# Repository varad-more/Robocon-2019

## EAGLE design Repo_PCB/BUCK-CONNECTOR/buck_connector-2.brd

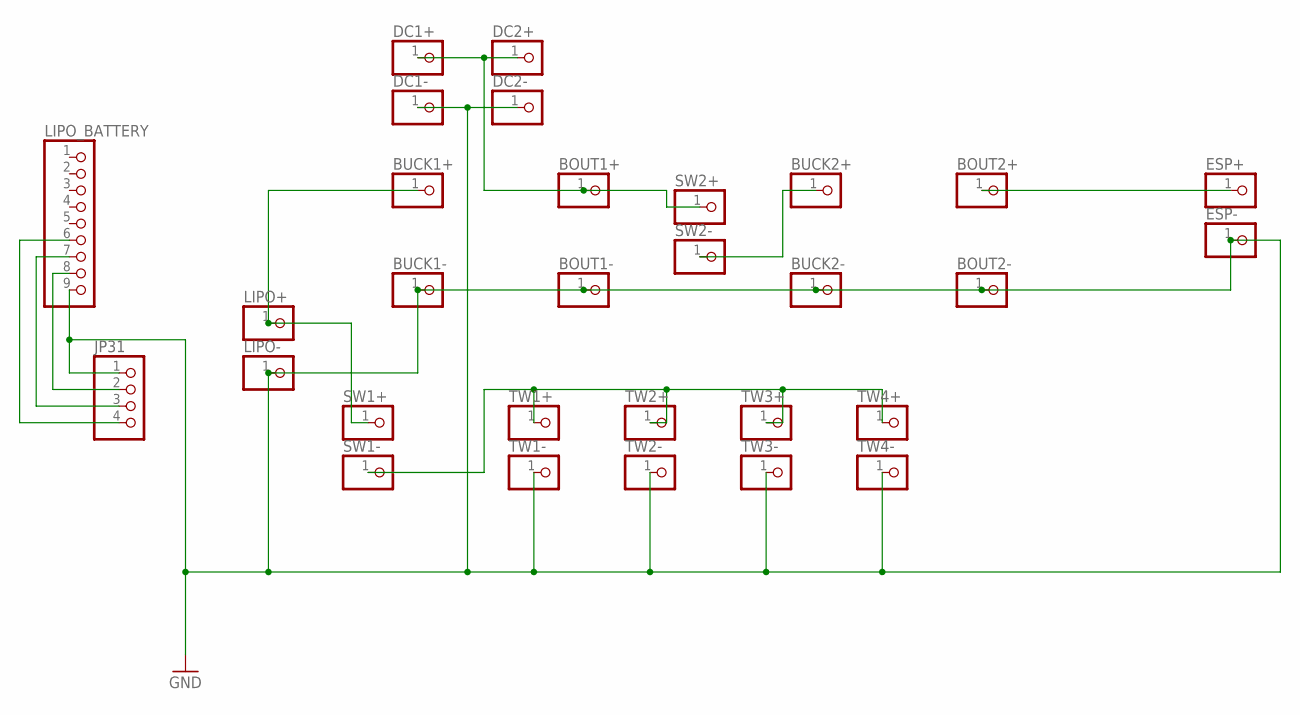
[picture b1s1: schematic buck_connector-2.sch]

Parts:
BOUT1+, BOUT1-, BOUT2+, BOUT2-: PINHD-1X1; 1X01
BUCK1+, BUCK1-, BUCK2+, BUCK2-: PINHD-1X1; 1X01
DC1+, DC1-, DC2+, DC2-: PINHD-1X1; 1X01
ESP+: PINHD-1X1; 1X01
ESP-: PINHD-1X1; 1X01
JP31: PINHD-1X4; 1X04
LIPO+: PINHD-1X1; 1X01
LIPO-: PINHD-1X1; 1X01
LIPO_BATTERY: PINHD-1X9; 1X09
SW1+, SW1-, SW2+, SW2-: PINHD-1X1; 1X01
TW1+, TW1-, TW2+, TW2-, TW3+, TW3-, TW4+, TW4-: PINHD-1X1; 1X01

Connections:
GND: BOUT1-.1, BOUT2-.1, BUCK1-.1, BUCK2-.1, DC1-.1, DC2-.1, ESP-.1, JP31.1, LIPO-.1, LIPO_BATTERY.9, TW1-.1, TW2-.1, TW3-.1, TW4-.1
unnamed: SW1-.1, TW1+.1, TW2+.1, TW3+.1, TW4+.1
unnamed: JP31.2, LIPO_BATTERY.8
unnamed: JP31.3, LIPO_BATTERY.7
unnamed: JP31.4, LIPO_BATTERY.6
unnamed: BOUT2+.1, ESP+.1
unnamed: BUCK1+.1, LIPO+.1, SW1+.1
unnamed: BOUT1+.1, DC1+.1, DC2+.1, SW2+.1
unnamed: BUCK2+.1, SW2-.1

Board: 2 copper layers, 30 parts (0 on the bottom side), 9 nets, no tracks yet.

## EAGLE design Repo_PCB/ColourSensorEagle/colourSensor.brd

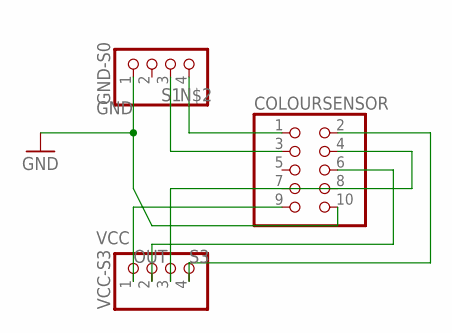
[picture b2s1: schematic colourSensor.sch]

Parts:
COLOURSENSOR: PINHD-2X5; 2X05
GND-S0: PINHD-1X4; 1X04
VCC-S3: PINHD-1X4; 1X04

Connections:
GND: COLOURSENSOR.10, GND-S0.1
unnamed: COLOURSENSOR.4, VCC-S3.3
unnamed: COLOURSENSOR.1, GND-S0.4
OUT: COLOURSENSOR.6, VCC-S3.2
S1: COLOURSENSOR.3, GND-S0.3
S3: COLOURSENSOR.2, VCC-S3.4
VCC: COLOURSENSOR.9, VCC-S3.1

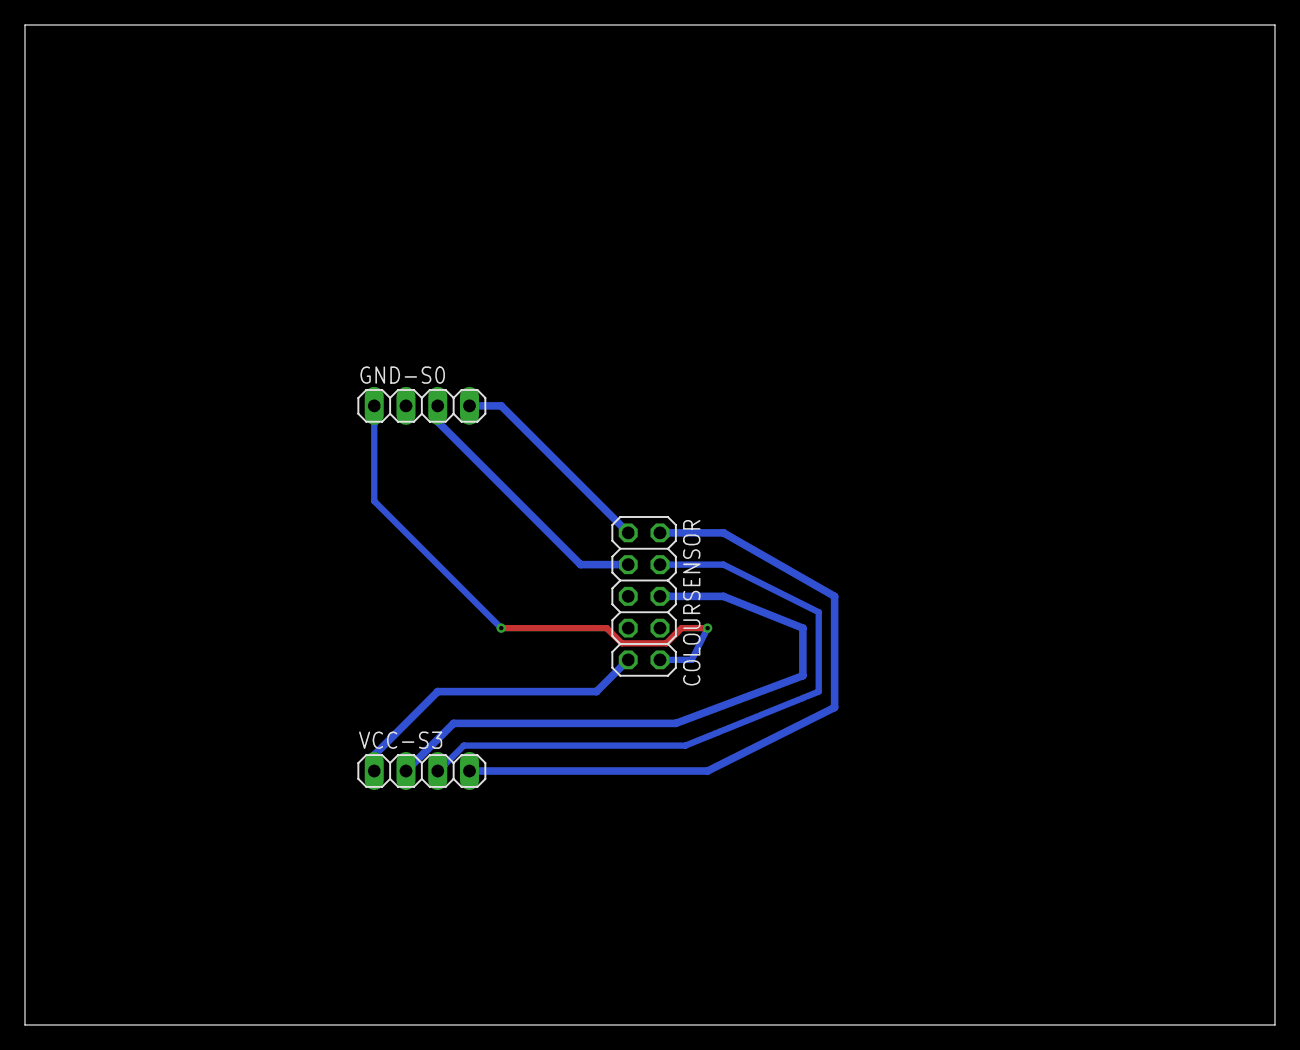
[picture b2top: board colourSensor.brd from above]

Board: 2 copper layers, 100.0 x 80.0 mm, 3 parts (0 on the bottom side), 7 nets.

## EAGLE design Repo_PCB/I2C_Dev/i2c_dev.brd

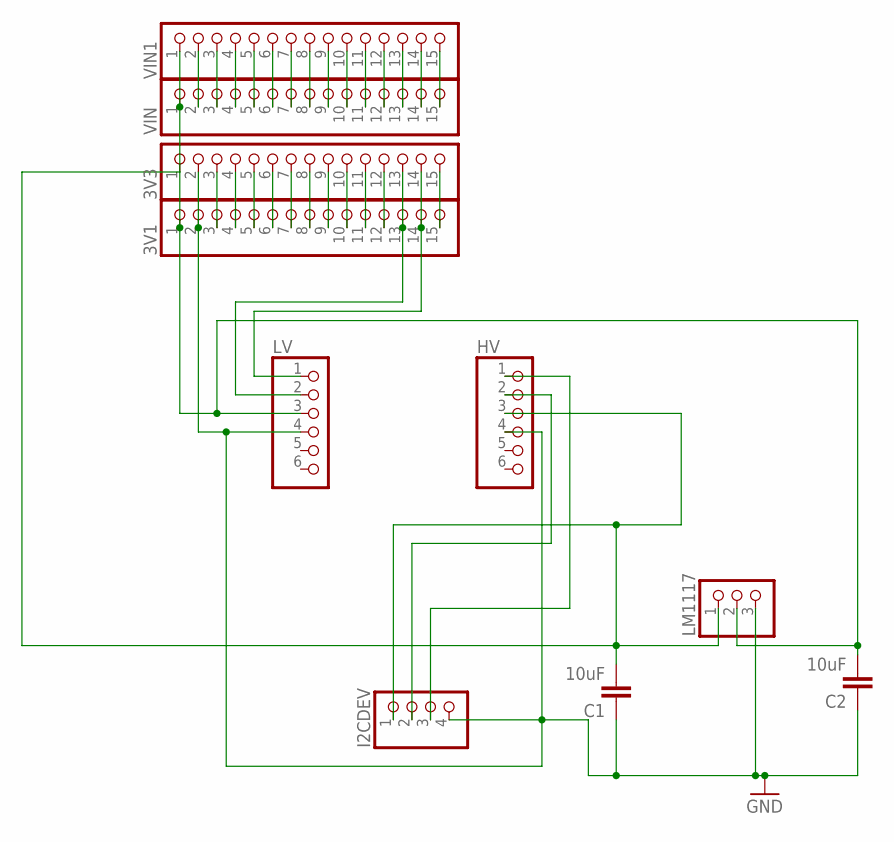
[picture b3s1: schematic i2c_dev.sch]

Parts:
3V1, 3V3: PINHD-1X15; 1X15
C1, C2: 10uF; C025-025X050
HV: PINHD-1X6; 1X06
I2CDEV: PINHD-1X4; 1X04
LM1117: PINHD-1X3; 1X03
LV: PINHD-1X6; 1X06
VIN, VIN1: PINHD-1X15; 1X15

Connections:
GND: 3V1.2, 3V3.2, C1.1, C2.1, HV.4, I2CDEV.4, LM1117.3, LV.4
I2C_DEV: HV.2, I2CDEV.2
unnamed: 3V1.14, 3V3.14, LV.1
unnamed: 3V1.1, 3V3.1, C2.2, LM1117.2, LV.3
unnamed: C1.2, HV.3, I2CDEV.1, LM1117.1, VIN.1, VIN1.1
unnamed: HV.1, I2CDEV.3
unnamed: 3V1.13, 3V3.13, LV.2
unnamed: VIN.15, VIN1.15
unnamed: VIN.14, VIN1.14
unnamed: VIN.13, VIN1.13
unnamed: VIN.12, VIN1.12
unnamed: VIN.11, VIN1.11
unnamed: VIN.10, VIN1.10
unnamed: VIN.9, VIN1.9
unnamed: VIN.8, VIN1.8
unnamed: VIN.7, VIN1.7
unnamed: VIN.6, VIN1.6
unnamed: VIN.5, VIN1.5
unnamed: VIN.4, VIN1.4
unnamed: VIN.3, VIN1.3
unnamed: VIN.2, VIN1.2
unnamed: 3V1.3, 3V3.3
unnamed: 3V1.4, 3V3.4
unnamed: 3V1.5, 3V3.5
unnamed: 3V1.6, 3V3.6
unnamed: 3V1.7, 3V3.7
unnamed: 3V1.8, 3V3.8
unnamed: 3V1.9, 3V3.9
unnamed: 3V1.10, 3V3.10
unnamed: 3V1.11, 3V3.11
unnamed: 3V1.12, 3V3.12
unnamed: 3V1.15, 3V3.15

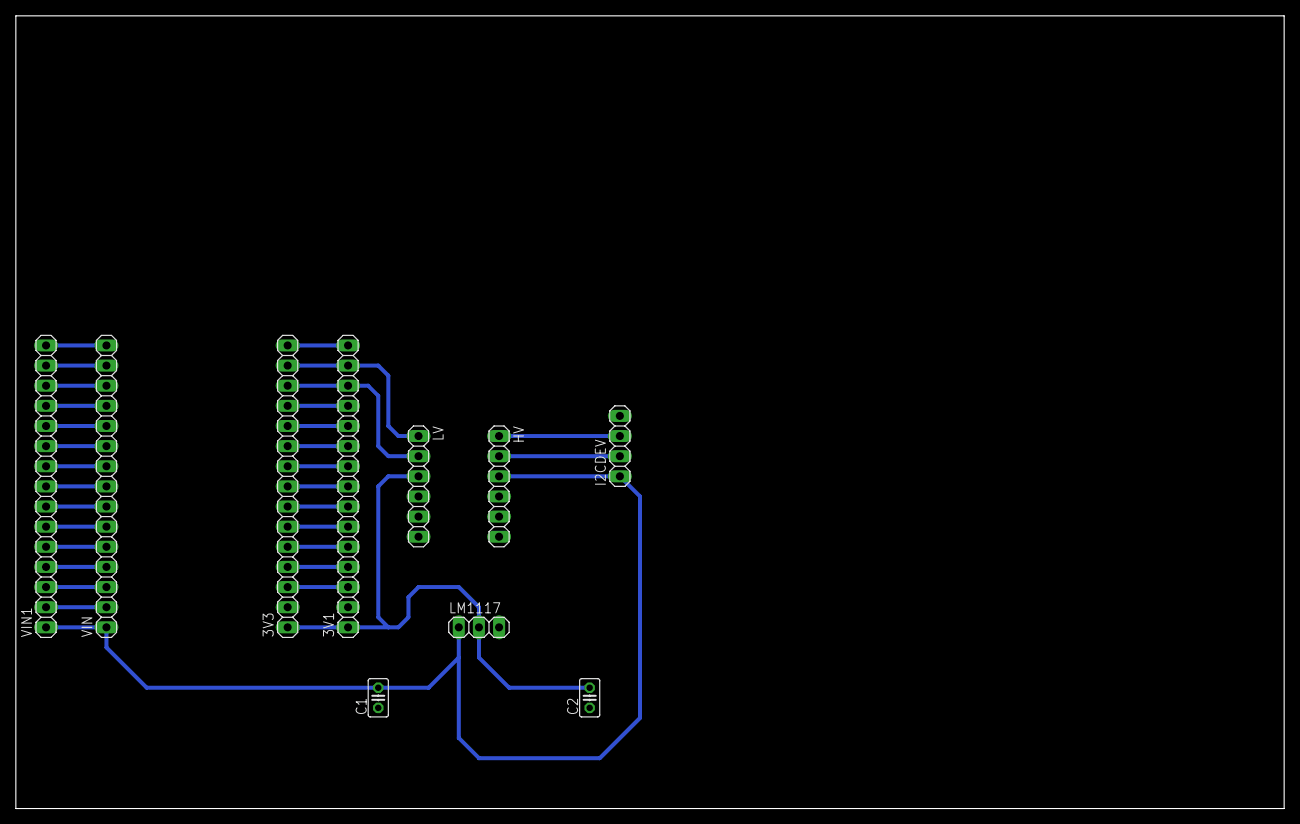
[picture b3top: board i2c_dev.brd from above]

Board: 2 copper layers, 160.0 x 100.0 mm, 10 parts (0 on the bottom side), 32 nets.

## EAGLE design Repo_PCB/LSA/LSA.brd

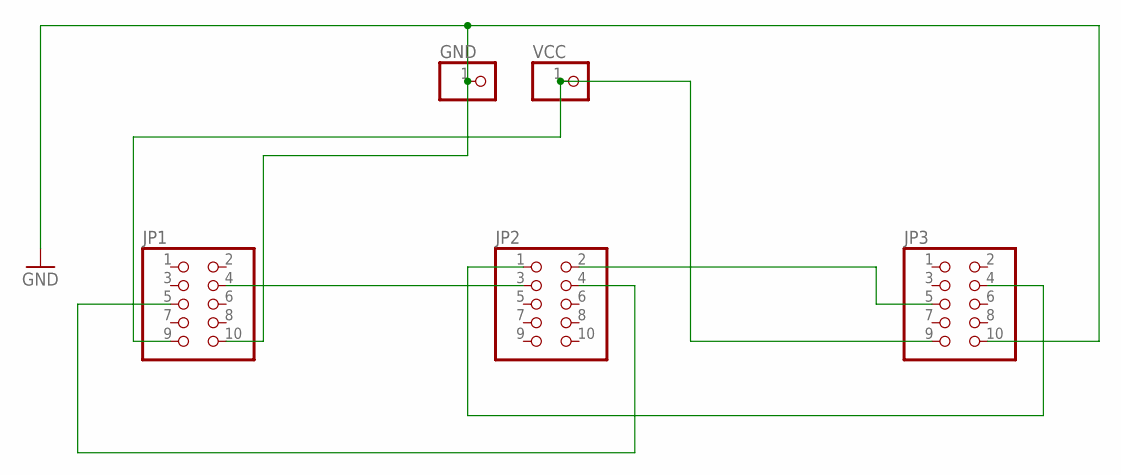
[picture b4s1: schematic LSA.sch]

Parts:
GND: PINHD-1X1; 1X01
JP1, JP2, JP3: PINHD-2X5; 2X05
VCC: PINHD-1X1; 1X01

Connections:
GND: GND.1, JP1.10, JP3.10
unnamed: JP2.2, JP3.5
unnamed: JP1.5, JP2.4
unnamed: JP1.9, JP3.9, VCC.1
unnamed: JP1.4, JP2.3
unnamed: JP2.1, JP3.4

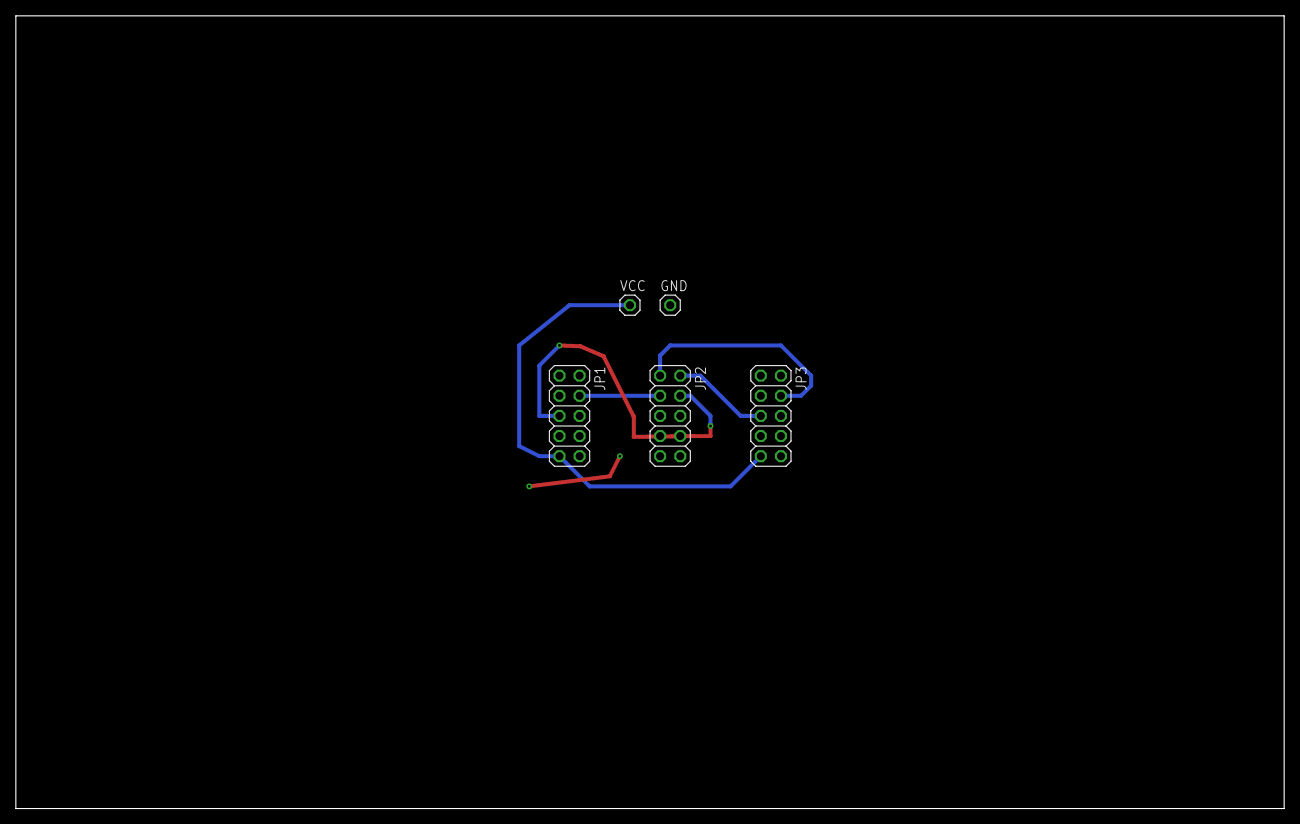
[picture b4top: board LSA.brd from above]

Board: 2 copper layers, 160.0 x 100.0 mm, 5 parts (0 on the bottom side), 6 nets.

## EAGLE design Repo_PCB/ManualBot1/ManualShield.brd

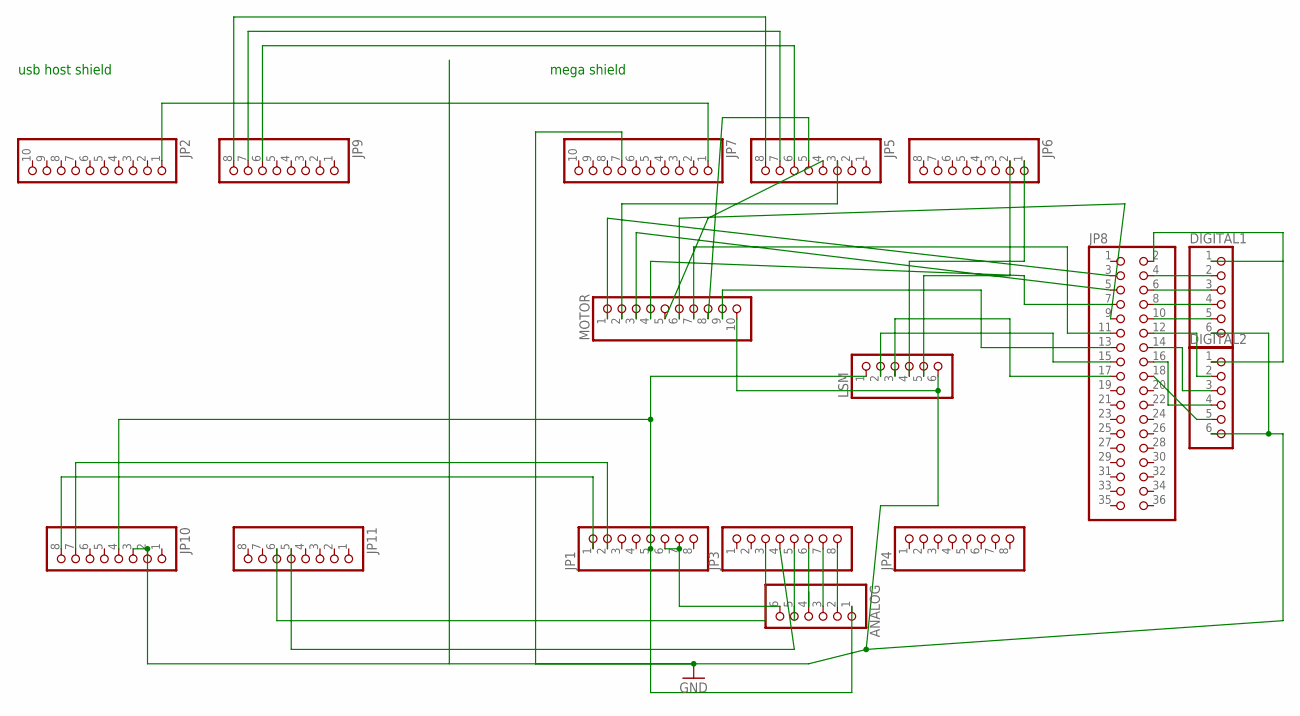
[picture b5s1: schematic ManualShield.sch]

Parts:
ANALOG: PINHD-1X6; 1X06
DIGITAL1, DIGITAL2: PINHD-1X6; 1X06
JP1, JP3, JP4, JP5, JP6, JP9, JP10, JP11: PINHD-1X8; 1X08
JP2, JP7: PINHD-1X10; 1X10
JP8: PINHD-2X18; 2X18
LSM: PINHD-1X6; 1X06
MOTOR: PINHD-1X10; 1X10

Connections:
GND: DIGITAL1.6, DIGITAL2.6, JP7.7, JP10.2, JP10.3, LSM.6, MOTOR.10
unnamed: JP6.2, LSM.5
unnamed: JP6.1, LSM.4
unnamed: ANALOG.1, JP1.5, JP10.4, LSM.1
unnamed: JP5.3, MOTOR.2
unnamed: JP5.4, MOTOR.5
unnamed: JP5.5, MOTOR.8
unnamed: DIGITAL1.2, JP8.4
unnamed: JP8.3, MOTOR.1
unnamed: JP8.5, MOTOR.3
unnamed: JP8.7, MOTOR.4
unnamed: JP8.9, MOTOR.6
unnamed: JP8.11, MOTOR.7
unnamed: JP8.13, MOTOR.9
unnamed: JP8.15, LSM.2
unnamed: JP8.17, LSM.3
unnamed: ANALOG.2, JP3.8
unnamed: ANALOG.3, JP3.7
unnamed: ANALOG.4, JP3.6
unnamed: ANALOG.5, JP3.5
unnamed: JP5.6, JP9.6
unnamed: JP5.7, JP9.7
unnamed: JP2.1, JP7.1
unnamed: DIGITAL1.3, JP8.6
unnamed: DIGITAL1.4, JP8.8
unnamed: DIGITAL1.5, JP8.10
unnamed: DIGITAL2.2, JP8.12
unnamed: DIGITAL2.3, JP8.14
unnamed: DIGITAL1.1, DIGITAL2.1, JP8.2
unnamed: DIGITAL2.4, JP8.16
unnamed: DIGITAL2.5, JP8.18
unnamed: JP5.8, JP9.8
unnamed: JP3.3, JP11.6
unnamed: JP3.4, JP11.5
unnamed: JP1.1, JP10.8
unnamed: JP1.2, JP10.7
unnamed: ANALOG.6, JP1.6, JP1.7

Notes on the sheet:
usb host shield
mega shield

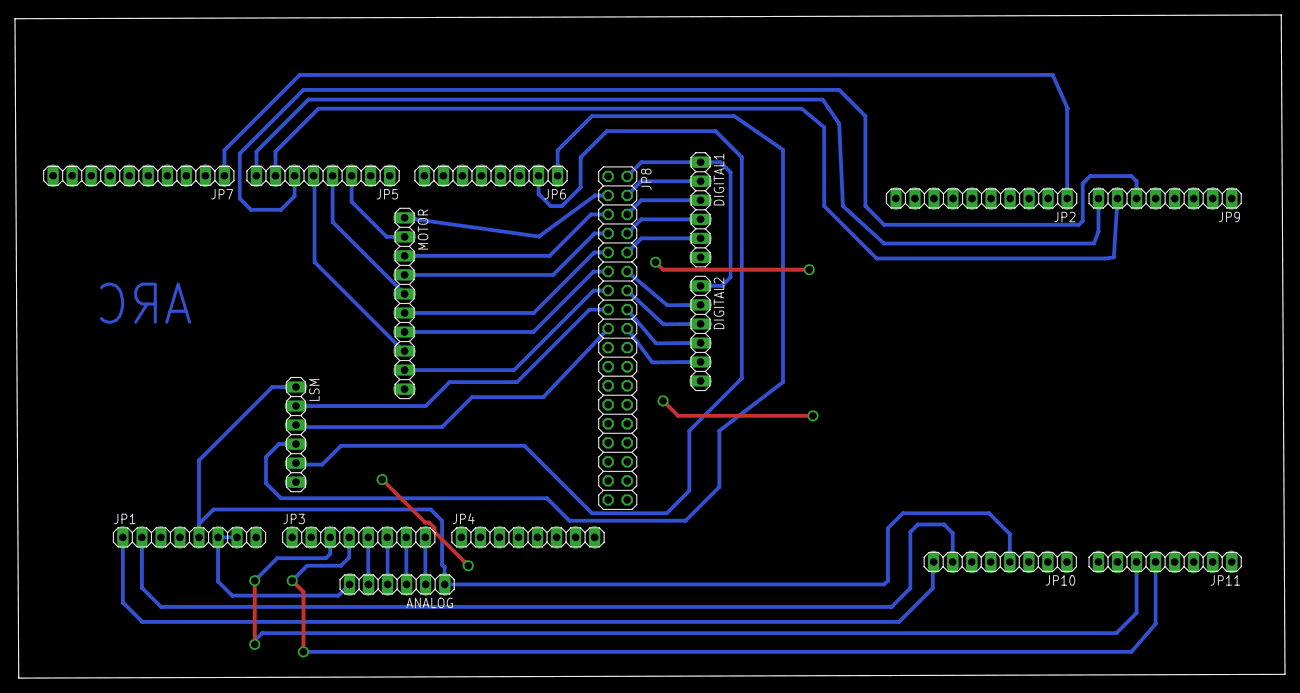
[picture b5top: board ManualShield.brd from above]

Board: 2 copper layers, 169.5 x 88.5 mm, 16 parts (0 on the bottom side), 37 nets.

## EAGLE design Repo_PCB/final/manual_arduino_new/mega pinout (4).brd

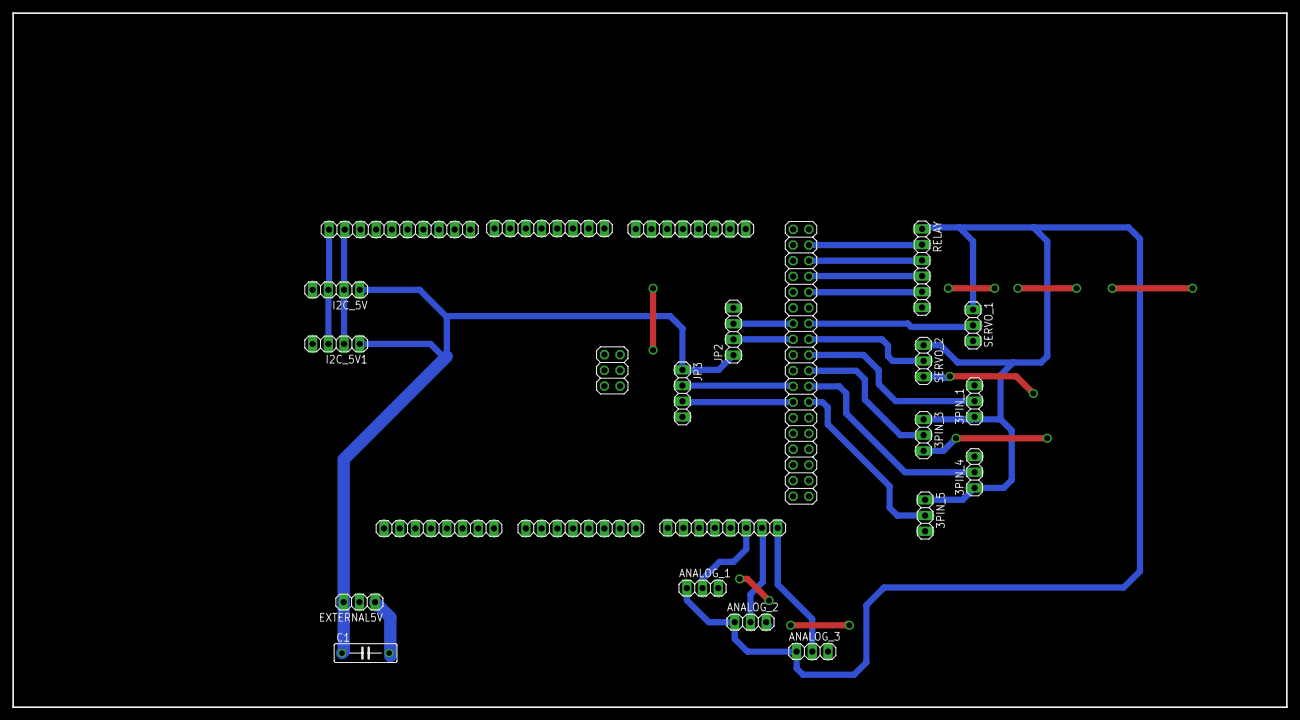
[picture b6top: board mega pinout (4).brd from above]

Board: 2 copper layers, 206.0 x 112.2 mm, 24 parts (0 on the bottom side), 22 nets.

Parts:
3PIN_1, 3PIN_3, 3PIN_4, 3PIN_5: 1X03
ANALOG_1, ANALOG_2, ANALOG_3: 1X03
C1: C075-032X103
EXTERNAL5V: 1X03
I2C_5V, I2C_5V1: 1X04
JP1: 2X18
JP2, JP3: 1X04
JP13: 1X10
JP14, JP15, JP16, JP17, JP18: 1X08
JP19: 2X03
RELAY: 1X06
SERVO_1, SERVO_2: 1X03

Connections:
5V: 3PIN_1.1, 3PIN_3.1, 3PIN_4.1, 3PIN_5.1, ANALOG_1.1, ANALOG_2.1, ANALOG_3.1, C1.1, EXTERNAL5V.3, I2C_5V.1, I2C_5V1.1, JP2.1, JP3.1, RELAY.1, SERVO_1.1, SERVO_2.1
23: JP1.4, RELAY.2
25: JP1.6, RELAY.3
27: JP1.8, RELAY.4
29: JP1.10, RELAY.5
31: JP1.14, SERVO_1.2
35: JP1.16, SERVO_2.2
37: 3PIN_1.2, JP1.18
39: 3PIN_3.2, JP1.20
40: JP1.21, JP3.2
41: 3PIN_4.2, JP1.22
42: JP1.23, JP3.3
43: 3PIN_5.2, JP1.24
A13: ANALOG_1.2, JP18.6
A14: ANALOG_2.2, JP18.7
A15: ANALOG_3.2, JP18.8
GND: 3PIN_1.3, 3PIN_3.3, 3PIN_4.3, 3PIN_5.3, ANALOG_1.3, ANALOG_2.3, ANALOG_3.3, C1.2, EXTERNAL5V.1, I2C_5V.4, I2C_5V1.4, JP1.1, JP1.2, JP2.4, JP3.4, JP16.7, RELAY.6, SERVO_1.3, SERVO_2.3
unnamed: JP1.15, JP2.2
unnamed: JP1.13, JP2.3
unnamed: JP1.35, JP1.36
SCL: I2C_5V.3, I2C_5V1.3, JP13.1
SDA: I2C_5V.2, I2C_5V1.2, JP13.2

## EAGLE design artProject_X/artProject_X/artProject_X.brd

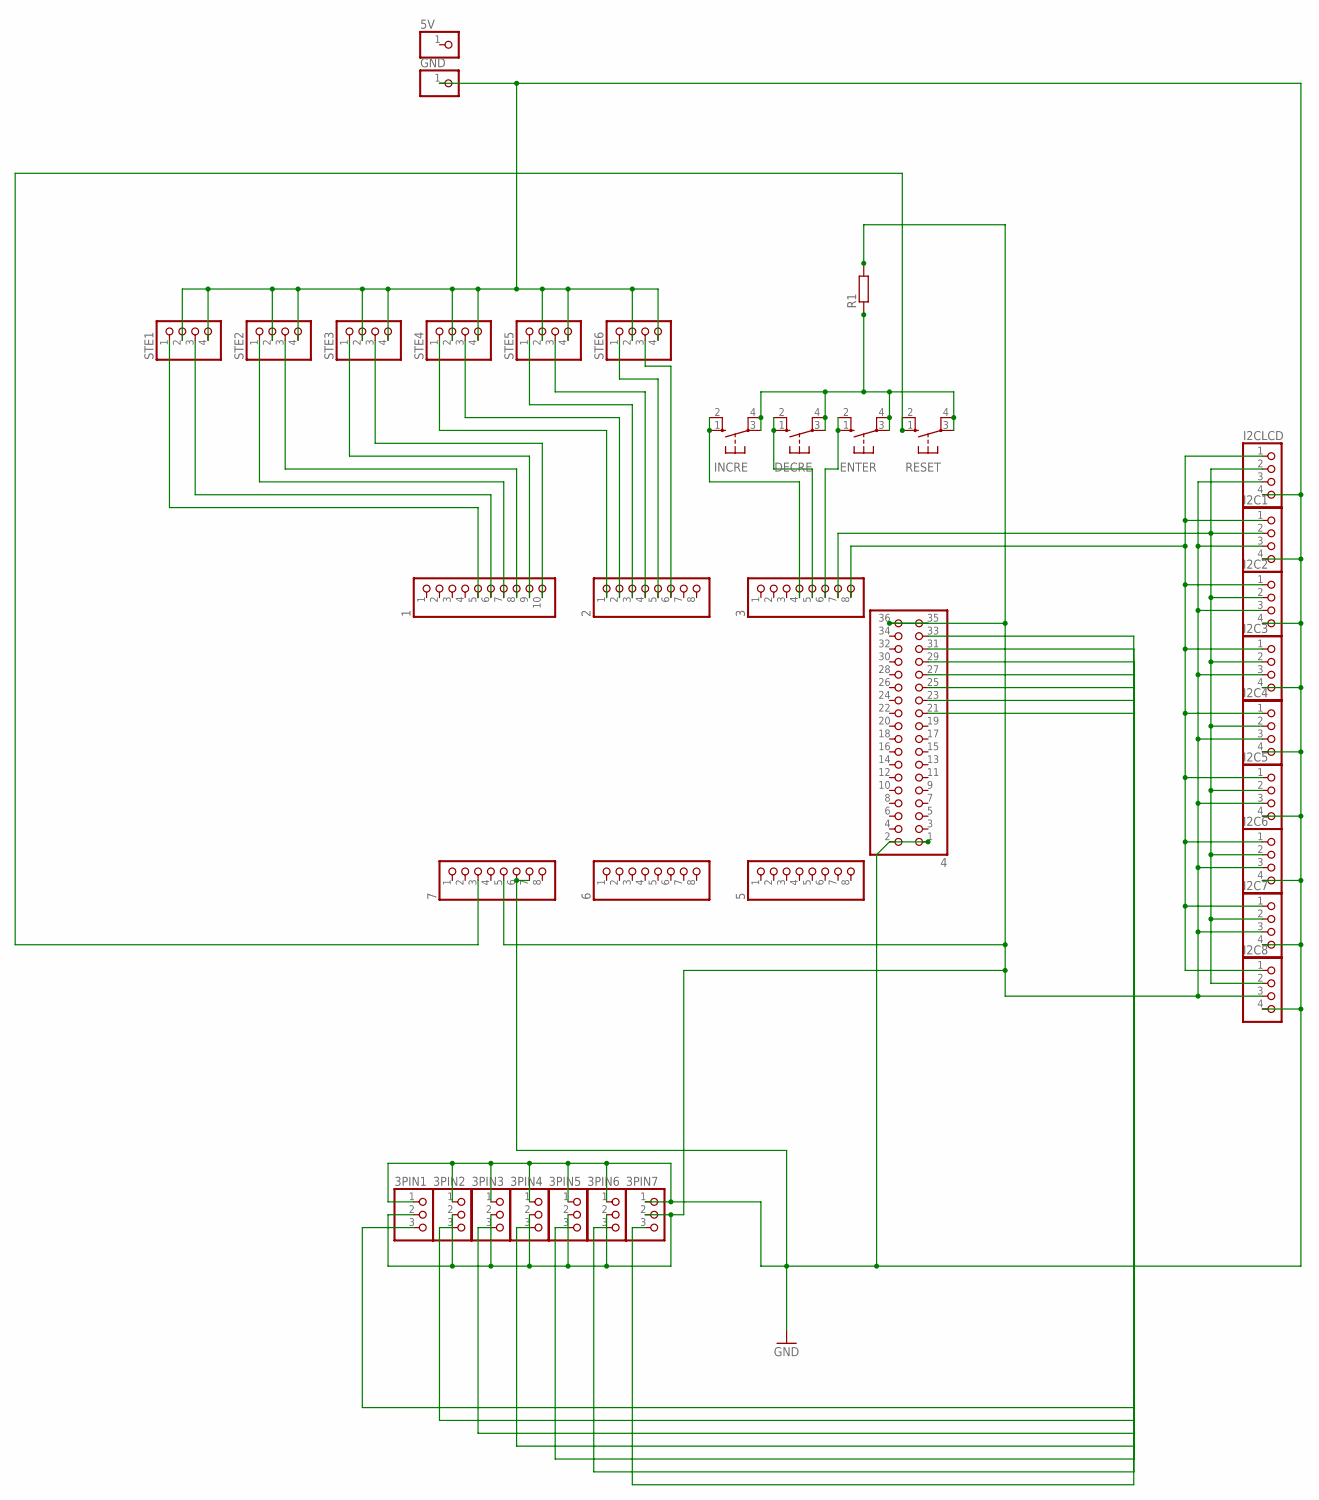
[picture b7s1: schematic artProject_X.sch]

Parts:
1: PINHD-1X10; 1X10
2, 3, 5, 6, 7: PINHD-1X8; 1X08
3PIN1, 3PIN2, 3PIN3, 3PIN4, 3PIN5, 3PIN6, 3PIN7: PINHD-1X3; 1X03
4: PINHD-2X18; 2X18
5V: PINHD-1X1; 1X01
DECRE: 10-XX; B3F-10XX
ENTER: 10-XX; B3F-10XX
GND: PINHD-1X1; 1X01
I2C1, I2C2, I2C3, I2C4, I2C5, I2C6, I2C7, I2C8, I2CLCD: PINHD-1X4; 1X04
INCRE: 10-XX; B3F-10XX
R1: R-EU_0204/7; 0204/7
RESET: 10-XX; B3F-10XX
STE1, STE2, STE3, STE4, STE5, STE6: PINHD-1X4; 1X04

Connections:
GND: 3PIN1.1, 3PIN2.1, 3PIN3.1, 3PIN4.1, 3PIN5.1, 3PIN6.1, 3PIN7.1, 4.1, 4.2, 7.6, 7.7, GND.1, I2C1.4, I2C2.4, I2C3.4, I2C4.4, I2C5.4, I2C6.4, I2C7.4, I2C8.4, I2CLCD.4, STE1.2, STE1.4, STE2.2, STE2.4, STE3.2, STE3.4, STE4.2, STE4.4, STE5.2, STE5.4, STE6.2, STE6.4
unnamed: 3PIN1.3, 4.33
unnamed: 3.4, INCRE.1 (S), INCRE.2 (S1)
unnamed: 3PIN2.3, 4.31
unnamed: 3PIN3.3, 4.29
unnamed: 3PIN4.3, 4.27
unnamed: 3PIN5.3, 4.25
unnamed: 3PIN6.3, 4.23
unnamed: 3PIN7.3, 4.21
unnamed: 3.5, DECRE.1 (S), DECRE.2 (S1)
unnamed: 3.6, ENTER.1 (S), ENTER.2 (S1)
unnamed: 7.3, RESET.1 (S), RESET.2 (S1)
unnamed: 2.5, STE6.1
unnamed: 2.6, STE6.3
unnamed: 2.4, STE5.3
unnamed: DECRE.3, DECRE.4 (P1), ENTER.3, ENTER.4 (P1), INCRE.3, INCRE.4 (P1), R1.1, RESET.3, RESET.4 (P1)
unnamed: 2.3, STE5.1
unnamed: 2.2, STE4.3
unnamed: 2.1, STE4.1
unnamed: 1.10, STE3.3
unnamed: 1.9, STE3.1
unnamed: 1.8, STE2.3
unnamed: 1.7, STE2.1
unnamed: 1.6, STE1.3
unnamed: 1.5, STE1.1
SCL: 3.8, I2C1.1, I2C2.1, I2C3.1, I2C4.1, I2C5.1, I2C6.1, I2C7.1, I2C8.1, I2CLCD.1
SDA: 3.7, I2C1.2, I2C2.2, I2C3.2, I2C4.2, I2C5.2, I2C6.2, I2C7.2, I2C8.2, I2CLCD.2
VCC: 3PIN1.2, 3PIN2.2, 3PIN3.2, 3PIN4.2, 3PIN5.2, 3PIN6.2, 3PIN7.2, 4.35, 4.36, 7.5, I2C1.3, I2C2.3, I2C3.3, I2C4.3, I2C5.3, I2C6.3, I2C7.3, I2C8.3, I2CLCD.3, R1.2

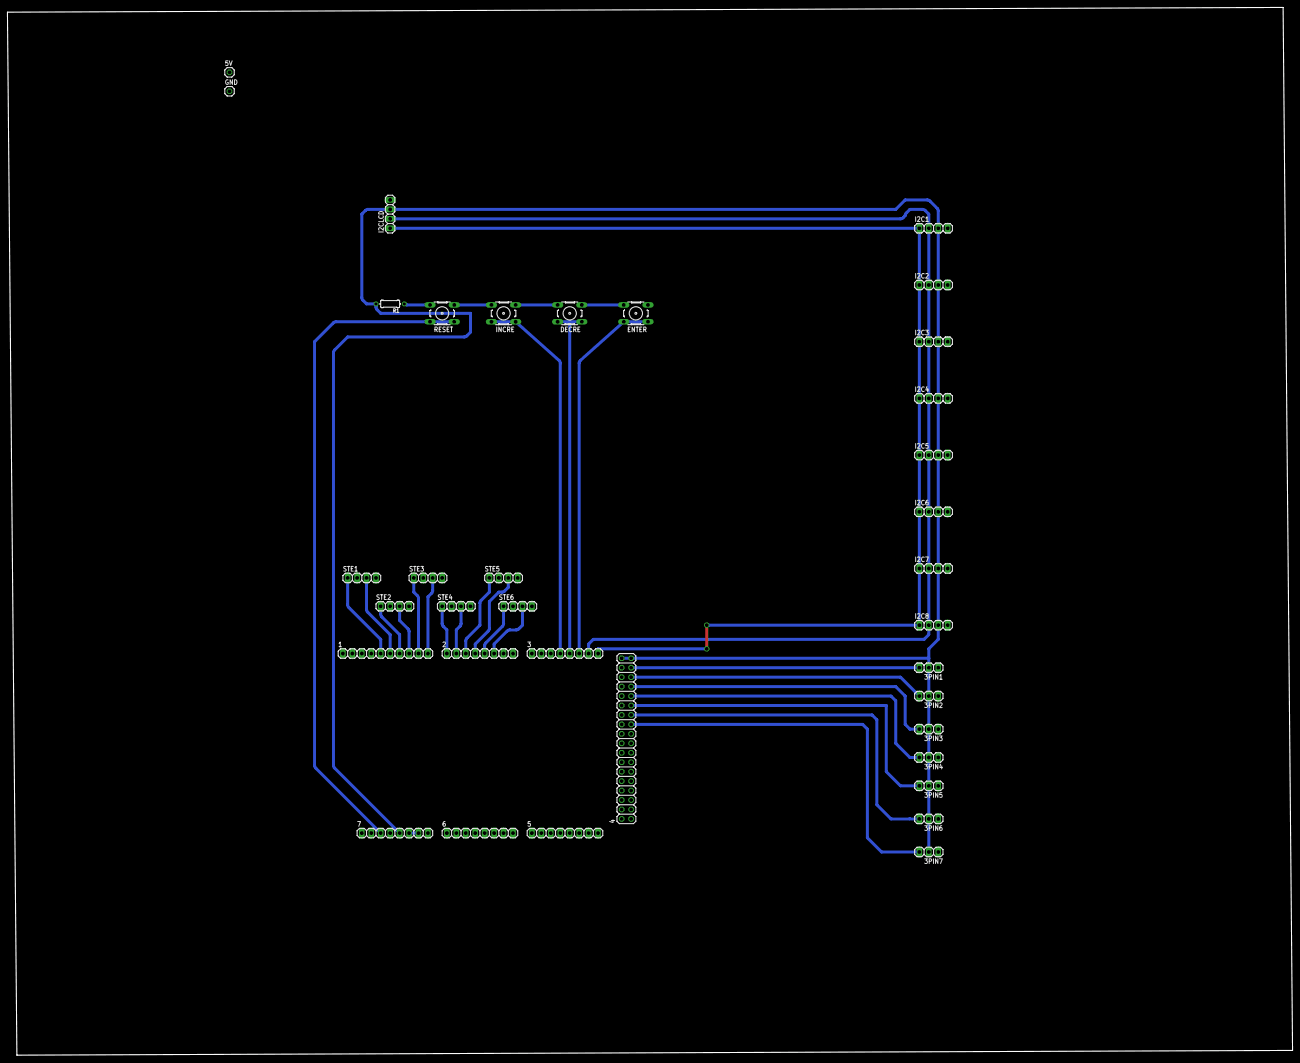
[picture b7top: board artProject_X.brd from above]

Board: 2 copper layers, 345.4 x 281.6 mm, 36 parts (0 on the bottom side), 28 nets.
